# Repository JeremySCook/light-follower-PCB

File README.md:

# light-follower-PCB
Light Following "Robot" as seen here: https://www.youtube.com/watch?v=BxwEkaiICWw

# Parts

Micro Gearmotor https://amzn.to/39SnwqA (Amazon Affiliate)  
CR2032 holder https://www.ebay.com/itm/10-pcs-Button-Cell-Sockets-CR2032-Vertical-Battery-Holders-Brass-Contact/264331560972  
LDRs  
Zip ties

PCBs available for purchase: https://www.tindie.com/products/JeremySCook/light-follower-robot-pcb/

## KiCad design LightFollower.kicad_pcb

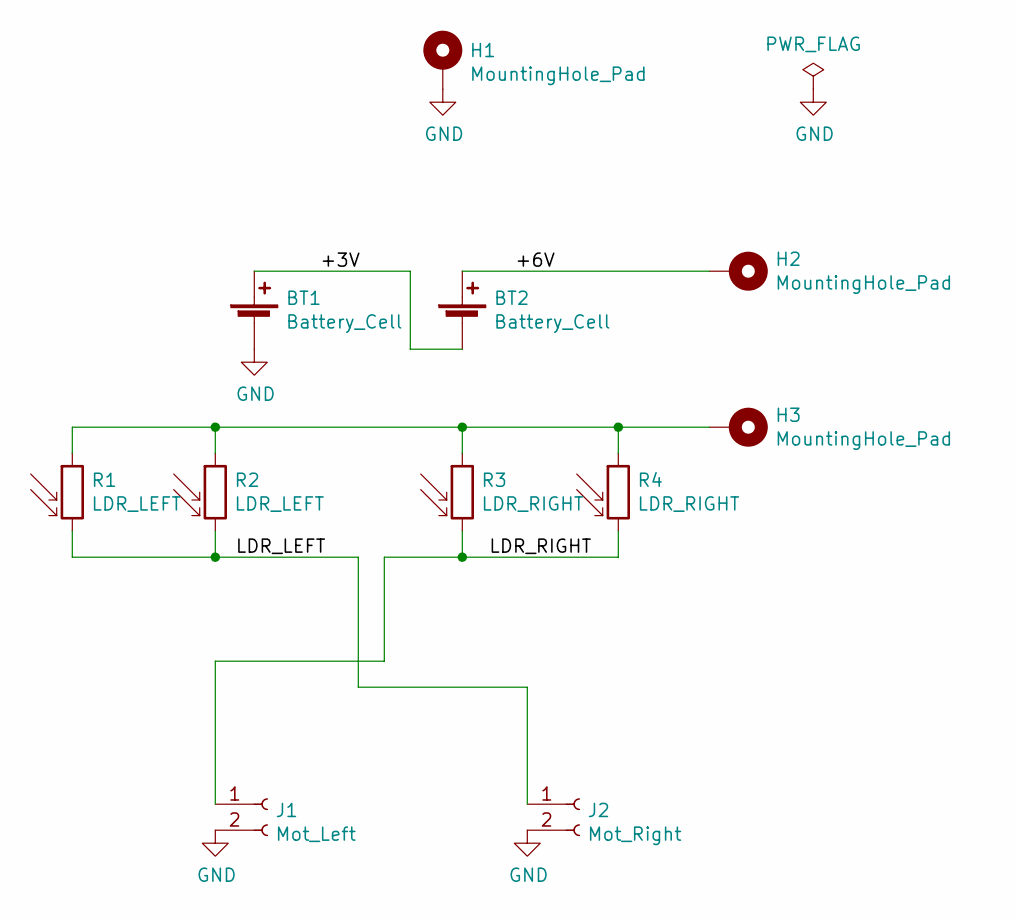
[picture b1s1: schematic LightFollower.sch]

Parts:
BT1, BT2: Battery_Cell; keytone1074-middle-ground
H1, H2, H3: MountingHole_Pad; MountingHole_2.2mm_M2_DIN965_Pad
J1: Mot_Left; PinHeader_1x02_P2.54mm_Vertical
J2: Mot_Right; PinHeader_1x02_P2.54mm_Vertical
R1, R2: LDR_LEFT; R_Axial_DIN0204_L3.6mm_D1.6mm_P1.90mm_Vertical
R3, R4: LDR_RIGHT; R_Axial_DIN0204_L3.6mm_D1.6mm_P1.90mm_Vertical

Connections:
/+3V: BT1.1 (+), BT2.2 (-)
/+6V: BT2.1 (+), H2.1
/LDR_LEFT: J2.1, R1.2, R2.2
/LDR_RIGHT: J1.1, R3.2, R4.2
GND: BT1.2 (-), H1.1, J1.2, J2.2
unnamed: H3.1, R1.1, R2.1, R3.1, R4.1

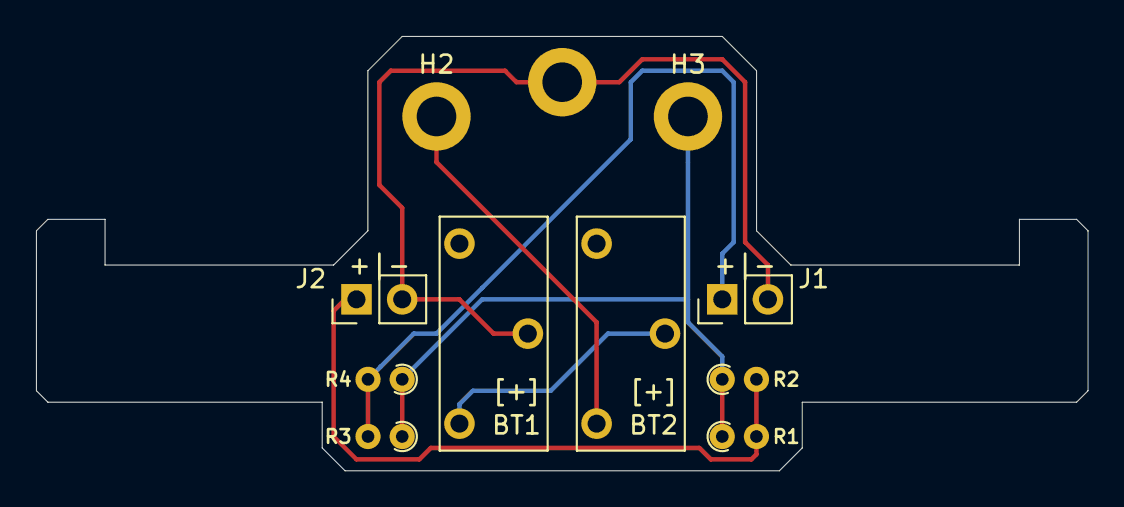
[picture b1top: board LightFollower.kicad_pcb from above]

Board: 2 copper layers, 58.4 x 24.1 mm, 11 parts (0 on the bottom side), 6 nets.
